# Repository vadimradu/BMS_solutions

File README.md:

# BMS_solutions
various bms solutions

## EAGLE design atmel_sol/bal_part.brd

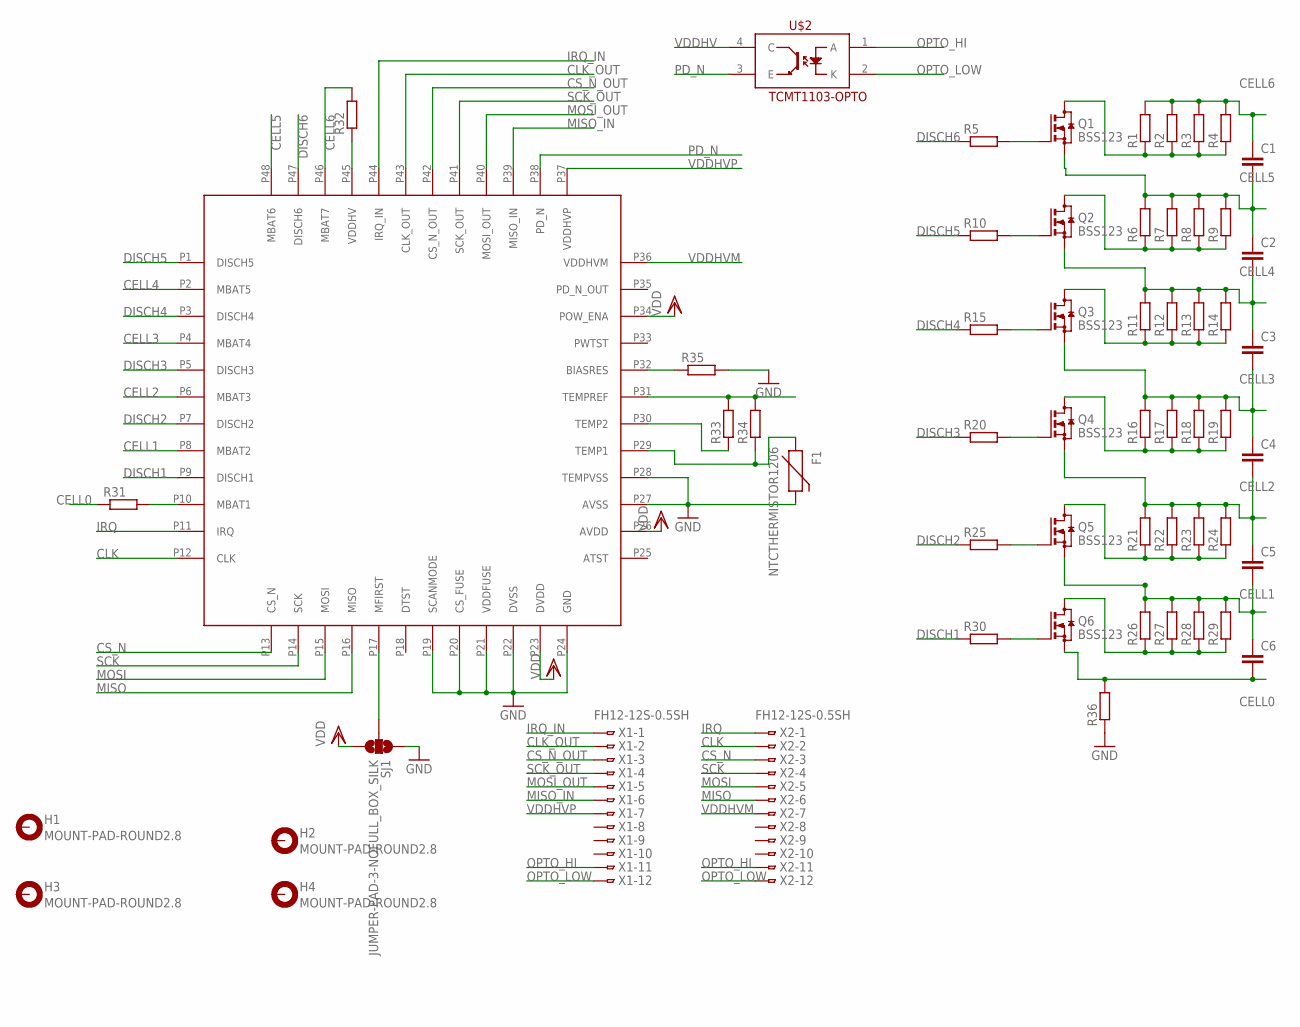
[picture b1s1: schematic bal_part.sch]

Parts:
C1, C2, C3, C4, C5, C6: C-EUC0805; C0805
F1: NTCTHERMISTOR1206; PTC-1206
H1, H2, H3, H4: MOUNT-PAD-ROUND2.8; 2,8-PAD
Q1, Q2, Q3, Q4, Q5, Q6: BSS123; SOT23
R1, R2, R3, R4, R6, R7, R8, R9, R11, R12, R13, R14, R16, R17, R18, R19, R21, R22, R23, R24, R26, R27, R28, R29: R-EU_R1206; R1206
R5, R10, R15, R20, R25, R30, R31, R32, R33, R34, R35, R36: R-EU_R0805; R0805
SJ1: JUMPER-PAD-3-NOFULL_BOX_SILK; PAD-JUMPER-3-NO_YES_SILK_FULL_BOX
U$1: ATA6870; QFN48
U$2: TCMT1103-OPTO; SSOP-4
X1, X2: FH12-12S-0.5SH

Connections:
CELL0: C6.2, Q6.2 (S), R31.1, R36.2
CELL1: C5.2, C6.1, Q5.2 (S), R26.2, R27.2, R28.2, R29.2, U$1.P8 (MBAT2)
CELL2: C4.2, C5.1, Q4.2 (S), R21.2, R22.2, R23.2, R24.2, U$1.P6 (MBAT3)
CELL3: C3.2, C4.1, Q3.2 (S), R16.2, R17.2, R18.2, R19.2, U$1.P4 (MBAT4)
CELL4: C2.2, C3.1, Q2.2 (S), R11.2, R12.2, R13.2, R14.2, U$1.P2 (MBAT5)
CELL5: C1.2, C2.1, Q1.2 (S), R6.2, R7.2, R8.2, R9.2, U$1.P48 (MBAT6)
CELL6: C1.1, R1.2, R2.2, R3.2, R4.2, R32.2, U$1.P46 (MBAT7)
CLK: U$1.P12 (CLK), X2.2
CLK_OUT: U$1.P43 (CLK_OUT), X1.2
CS_N: U$1.P13 (CS_N), X2.3
CS_N_OUT: U$1.P42 (CS_N_OUT), X1.3
DISCH1: R30.1, U$1.P9 (DISCH1)
DISCH2: R25.1, U$1.P7 (DISCH2)
DISCH3: R20.1, U$1.P5 (DISCH3)
DISCH4: R15.1, U$1.P3 (DISCH4)
DISCH5: R10.1, U$1.P1 (DISCH5)
DISCH6: R5.1, U$1.P47 (DISCH6)
GND: F1.2, R35.2, R36.1, SJ1.1, U$1.P19 (SCANMODE), U$1.P20 (CS_FUSE), U$1.P21 (VDDFUSE), U$1.P22 (DVSS), U$1.P24 (GND), U$1.P27 (AVSS), U$1.P28 (TEMPVSS)
IRQ: U$1.P11 (IRQ), X2.1
IRQ_IN: U$1.P44 (IRQ_IN), X1.1
MISO: U$1.P16 (MISO), X2.6
MISO_IN: U$1.P39 (MISO_IN), X1.6
MOSI: U$1.P15 (MOSI), X2.5
MOSI_OUT: U$1.P40 (MOSI_OUT), X1.5
unnamed: Q1.3 (D), R1.1, R2.1, R3.1, R4.1
unnamed: Q1.1 (G), R5.2
unnamed: Q2.3 (D), R6.1, R7.1, R8.1, R9.1
unnamed: Q2.1 (G), R10.2
unnamed: Q3.3 (D), R11.1, R12.1, R13.1, R14.1
unnamed: Q3.1 (G), R15.2
unnamed: Q4.3 (D), R16.1, R17.1, R18.1, R19.1
unnamed: Q4.1 (G), R20.2
unnamed: Q5.3 (D), R21.1, R22.1, R23.1, R24.1
unnamed: Q5.1 (G), R25.2
unnamed: Q6.3 (D), R26.1, R27.1, R28.1, R29.1
unnamed: Q6.1 (G), R30.2
unnamed: R31.2, U$1.P10 (MBAT1)
unnamed: R33.2, R34.2, U$1.P31 (TEMPREF)
unnamed: R33.1, U$1.P30 (TEMP2)
unnamed: F1.1, R34.1, U$1.P29 (TEMP1)
unnamed: R35.1, U$1.P32 (BIASRES)
unnamed: SJ1.2, U$1.P17 (MFIRST)
OPTO_HI: U$2.1 (A), X1.11, X2.11
OPTO_LOW: U$2.2 (K), X1.12, X2.12
PD_N: U$1.P38 (PD_N), U$2.3 (E)
SCK: U$1.P14 (SCK), X2.4
SCK_OUT: U$1.P41 (SCK_OUT), X1.4
VDD: SJ1.3, U$1.P23 (DVDD), U$1.P26 (AVDD), U$1.P34 (POW_ENA)
VDDHV: R32.1, U$1.P45 (VDDHV), U$2.4 (C)
VDDHVM: U$1.P36 (VDDHVM), X2.7
VDDHVP: U$1.P37 (VDDHVP), X1.7

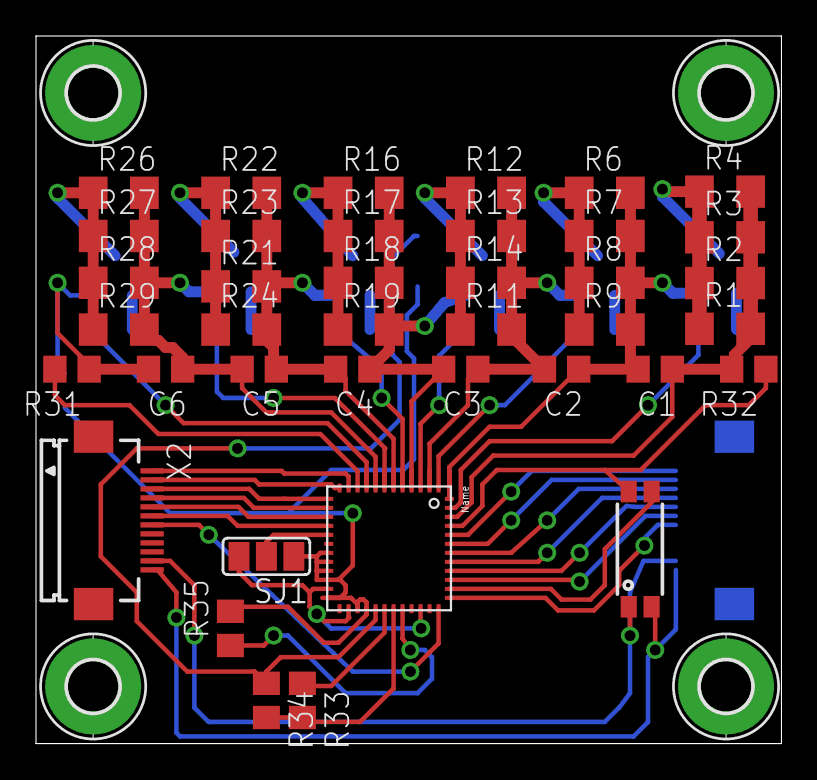
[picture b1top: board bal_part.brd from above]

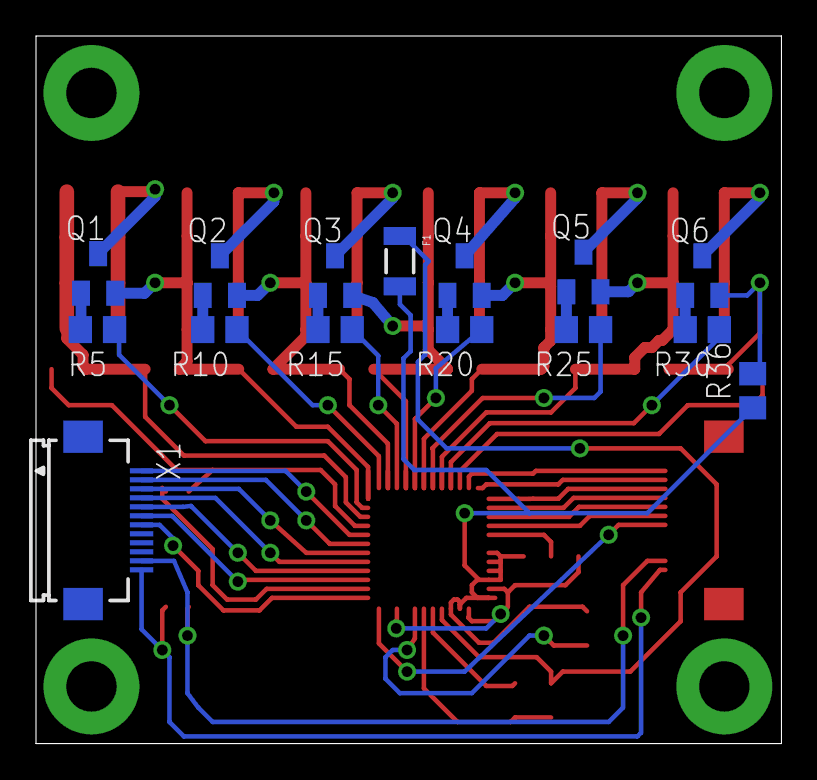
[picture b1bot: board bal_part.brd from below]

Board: 2 copper layers, 41.4 x 39.3 mm, 58 parts (15 on the bottom side), 51 nets.

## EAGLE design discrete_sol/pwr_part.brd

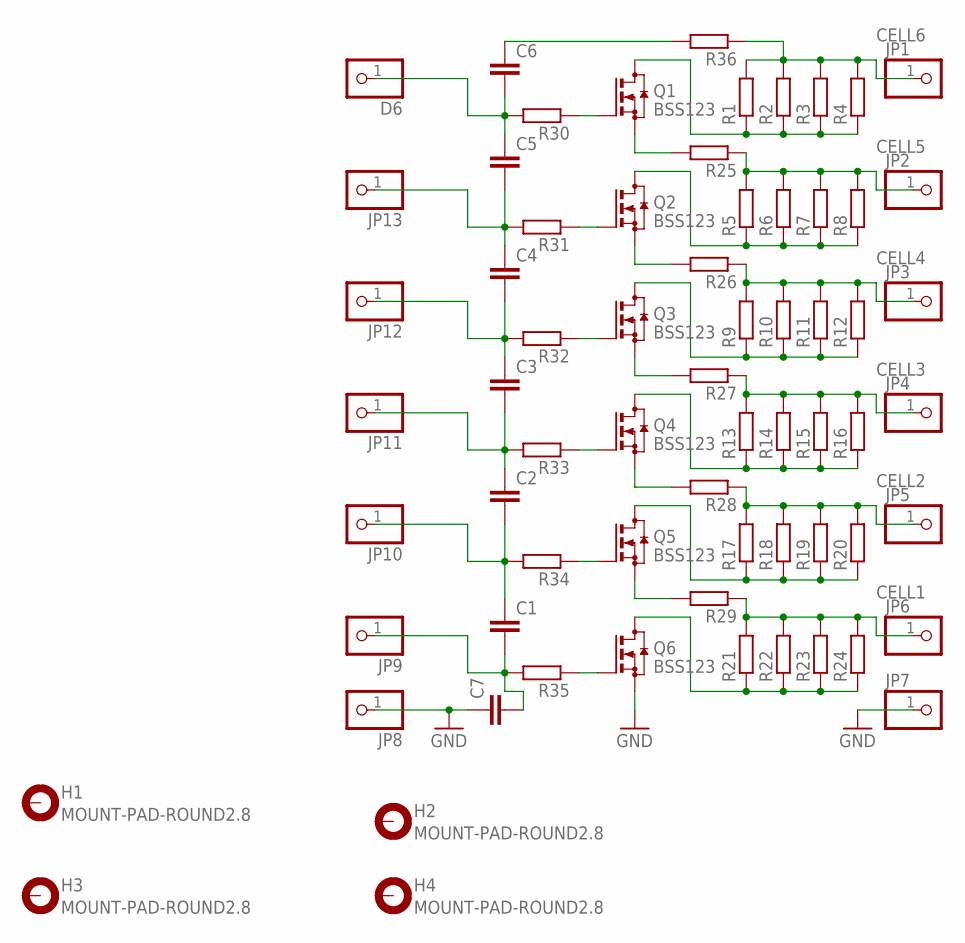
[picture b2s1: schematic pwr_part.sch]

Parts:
C1, C2, C3, C4, C5, C6, C7: C-EUC0805K; C0805K
D6: PINHD-1X1; 1X01
H1, H2, H3, H4: MOUNT-PAD-ROUND2.8; 2,8-PAD
JP1, JP2, JP3, JP4, JP5, JP6, JP7, JP8, JP9, JP10, JP11, JP12, JP13: PINHD-1X1; 1X01
Q1, Q2, Q3, Q4, Q5, Q6: BSS123; SOT23
R1, R2, R3, R4, R5, R6, R7, R8, R9, R10, R11, R12, R13, R14, R15, R16, R17, R18, R19, R20, R21, R22, R23, R24, R30, R31, R32, R33, R34, R35: R-EU_R1206; R1206
R25, R26, R27, R28, R29, R36: R-EU_0411/3V; 0411V

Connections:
CELL1: JP6.1, R21.2, R22.2, R23.2, R24.2, R29.1
CELL2: JP5.1, R17.2, R18.2, R19.2, R20.2, R28.1
CELL3: JP4.1, R13.2, R14.2, R15.2, R16.2, R27.1
CELL4: JP3.1, R9.2, R10.2, R11.2, R12.2, R26.1
CELL5: JP2.1, R5.2, R6.2, R7.2, R8.2, R25.1
CELL6: JP1.1, R1.2, R2.2, R3.2, R4.2, R36.1
D5: C4.1, C5.2, JP13.1, R31.2
GND: C7.1, JP7.1, JP8.1, Q6.2 (S)
unnamed: Q1.3 (D), R1.1, R2.1, R3.1, R4.1
unnamed: C6.1, R36.2
unnamed: Q2.3 (D), R5.1, R6.1, R7.1, R8.1
unnamed: Q3.3 (D), R9.1, R10.1, R11.1, R12.1
unnamed: Q4.3 (D), R13.1, R14.1, R15.1, R16.1
unnamed: Q5.3 (D), R17.1, R18.1, R19.1, R20.1
unnamed: Q6.3 (D), R21.1, R22.1, R23.1, R24.1
unnamed: Q2.2 (S), R26.2
unnamed: Q3.2 (S), R27.2
unnamed: Q4.2 (S), R28.2
unnamed: Q5.2 (S), R29.2
unnamed: Q1.1 (G), R30.1
unnamed: Q1.2 (S), R25.2
unnamed: Q2.1 (G), R31.1
unnamed: Q3.1 (G), R32.1
unnamed: Q4.1 (G), R33.1
unnamed: Q5.1 (G), R34.1
unnamed: Q6.1 (G), R35.1
unnamed: C5.1, C6.2, D6.1, R30.2
unnamed: C3.1, C4.2, JP12.1, R32.2
unnamed: C2.1, C3.2, JP11.1, R33.2
unnamed: C1.1, C2.2, JP10.1, R34.2
unnamed: C1.2, C7.2, JP9.1, R35.2

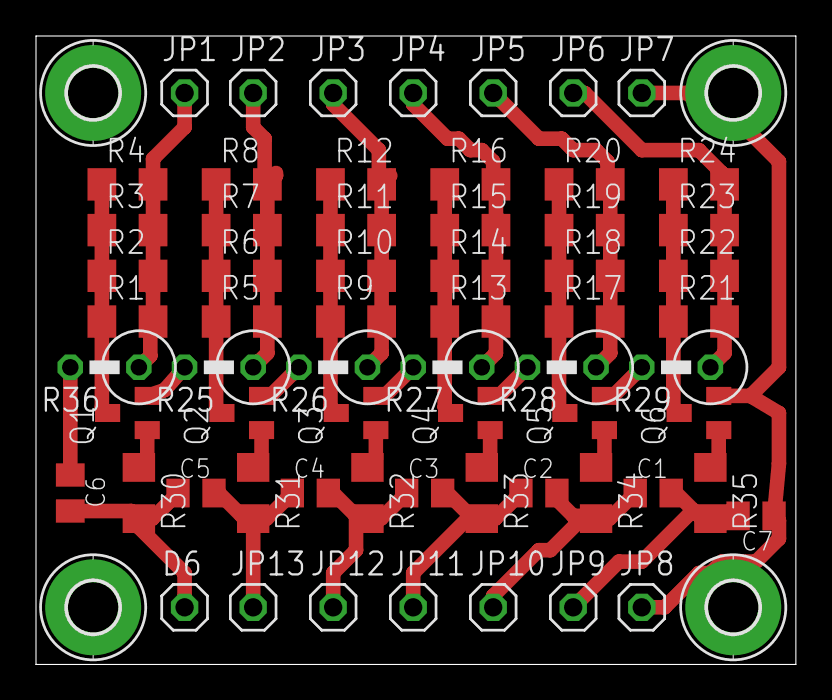
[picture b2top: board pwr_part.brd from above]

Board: 2 copper layers, 42.2 x 34.9 mm, 67 parts (0 on the bottom side), 31 nets.

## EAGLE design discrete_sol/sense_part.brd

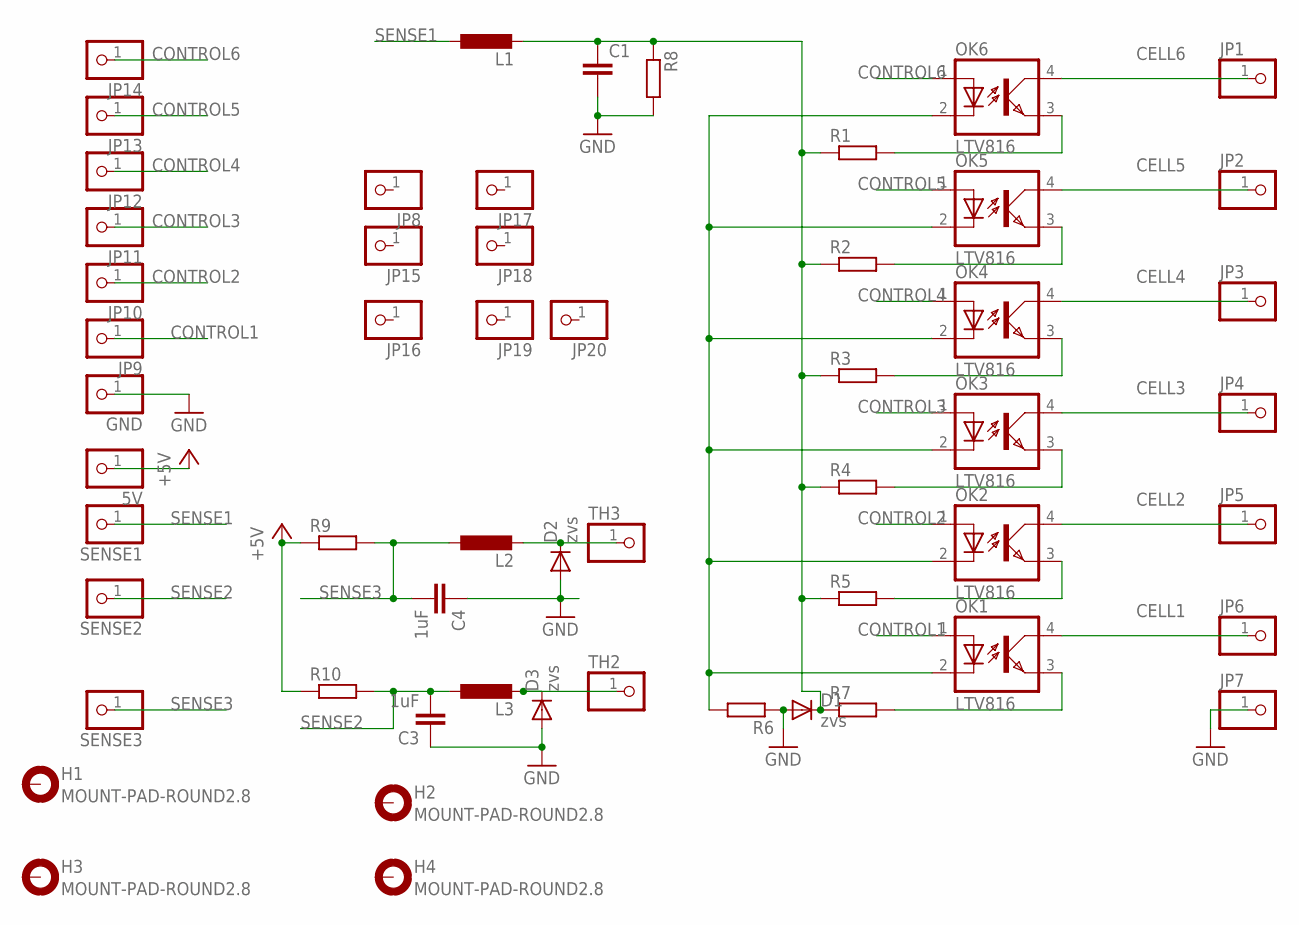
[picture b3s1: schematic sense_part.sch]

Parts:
5V: PINHD-1X1; 1X01
C1: C-EU050-030X075; C050-030X075
C3, C4: 1uF; C025-024X044
D1, D2, D3: zvs; SOD-123_MINI-SMA
GND: PINHD-1X1; 1X01
H1, H2, H3, H4: MOUNT-PAD-ROUND2.8; 2,8-PAD
JP1, JP2, JP3, JP4, JP5, JP6, JP7, JP8, JP9, JP10, JP11, JP12, JP13, JP14, JP15, JP16, JP17, JP18, JP19, JP20: PINHD-1X1; 1X01
L1, L2, L3: L-EU0207/12; 0207/12
OK1, OK2, OK3, OK4, OK5, OK6: LTV816; DIL04
R1, R2, R3, R4, R5, R6, R7, R8, R9, R10: R-EU_R1206; R1206
SENSE1, SENSE2, SENSE3: PINHD-1X1; 1X01
TH2, TH3: PINHD-1X1; 1X01

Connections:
+5V: 5V.1, R9.1, R10.1
CELL1: JP6.1, OK1.4 (COL)
CELL2: JP5.1, OK2.4 (COL)
CELL3: JP4.1, OK3.4 (COL)
CELL4: JP3.1, OK4.4 (COL)
CELL5: JP2.1, OK5.4 (COL)
CELL6: JP1.1, OK6.4 (COL)
CONTROL1: JP9.1, OK1.1 (A)
CONTROL2: JP10.1, OK2.1 (A)
CONTROL3: JP11.1, OK3.1 (A)
CONTROL4: JP12.1, OK4.1 (A)
CONTROL5: JP13.1, OK5.1 (A)
CONTROL6: JP14.1, OK6.1 (A)
GND: C1.2, C3.1, C4.1, D1.A, D2.A, D3.A, GND.1, JP7.1, R6.1, R8.2
unnamed: OK1.2 (C), OK2.2 (C), OK3.2 (C), OK4.2 (C), OK5.2 (C), OK6.2 (C), R6.2
unnamed: OK2.3 (EMIT), R5.2
unnamed: OK3.3 (EMIT), R4.2
unnamed: OK4.3 (EMIT), R3.2
unnamed: OK5.3 (EMIT), R2.2
unnamed: OK6.3 (EMIT), R1.2
unnamed: D3.C, L3.2, TH2.1
unnamed: OK1.3 (EMIT), R7.2
unnamed: C1.1, D1.C, L1.2, R1.1, R2.1, R3.1, R4.1, R5.1, R7.1, R8.1
unnamed: D2.C, L2.2, TH3.1
SENSE1: L1.1, SENSE1.1
SENSE2: C3.2, L3.1, R10.2, SENSE2.1
SENSE3: C4.2, L2.1, R9.2, SENSE3.1

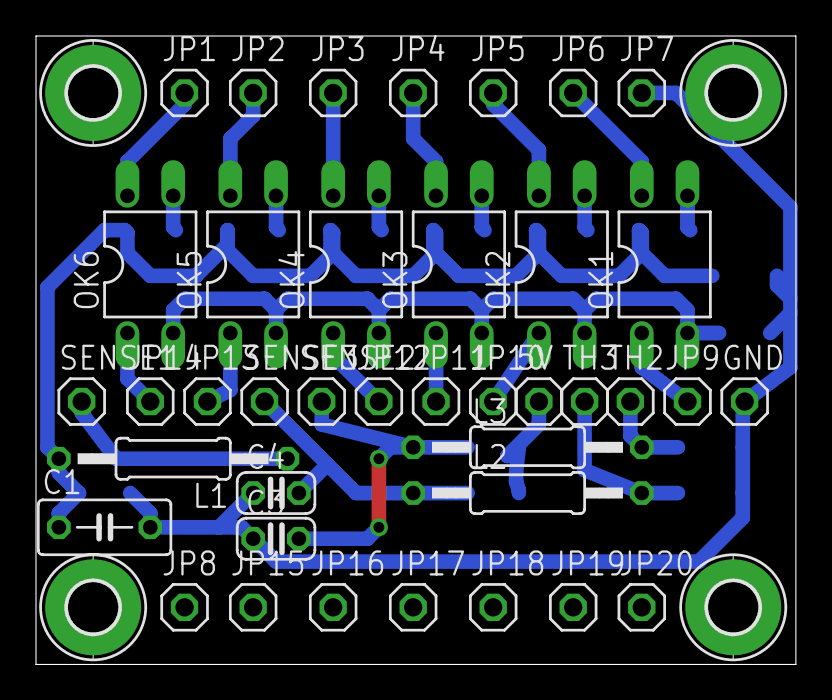
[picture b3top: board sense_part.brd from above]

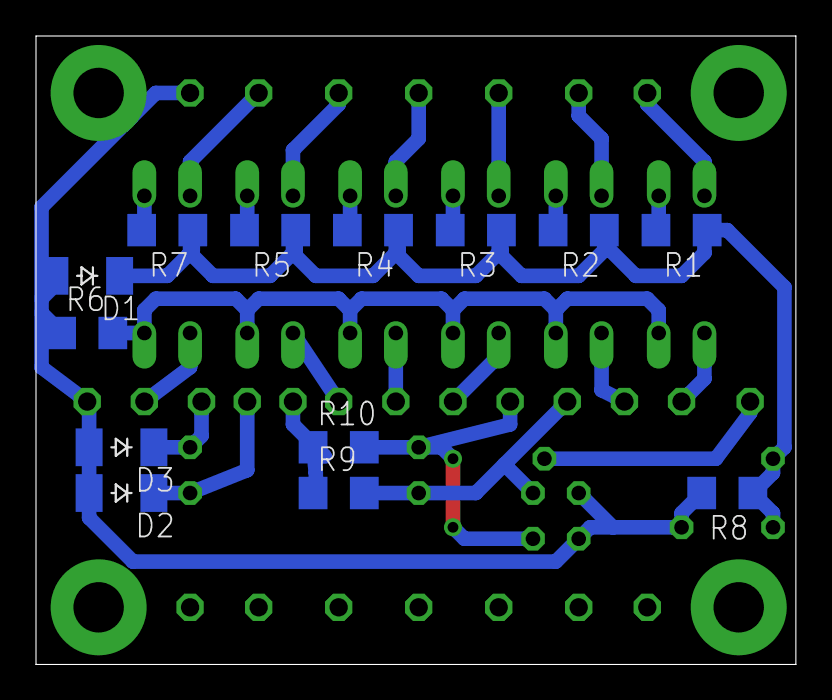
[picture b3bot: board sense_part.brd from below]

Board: 2 copper layers, 42.2 x 34.9 mm, 56 parts (13 on the bottom side), 27 nets.

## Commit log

2015-07-16 first upload
2015-07-20 second edit
2015-07-21 first working prototype
2015-07-21 improved documentation
2015-07-21 added garbage detection
2015-07-26 footprint ata6870

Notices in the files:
parts and their libraries:
SparkFun-PowerIC: Licensing: Creative Commons ShareAlike 4.0 International - https://creativecommons.org/licenses/by-sa/4.0
